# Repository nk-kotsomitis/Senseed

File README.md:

## Introduction

Senseed, a Smart Agriculture IoT System, is an end-to-end IoT solution designed to monitor and manage agricultural environments. This repository includes the **firmware**, **hardware**, **enclosures**, and **server setup** required to deploy the system.<br>
<br>
<br>
<div align="center">
  
</div>
<br>
<br>

## System Overview
This system leverages a wireless sensor network in a star topology, using **NRF24L01** modules operating at 2.4GHz for communication. The network comprises soil and environmental sensors that gather data and transmit it to a central gateway. The gateway serves as the primary hub, collecting sensor data and communicating with the controllers to make real-time adjustments. <br>
<br>
For data processing and storage, the gateway connects to an Ubuntu server over **WiFi**, using the **MQTT** protocol with **RabbitMQ** as the message broker. On the server side, **InfluxDB** is used for time-series data storage. <br>

<br>
<br>
<div align="center">
  
</div>
<br>
<br>

The gateway is powered by an **ATMEGA1284** and connects to the internet via an **ESP32** module, utilizing AT commands. The sensors and controllers in the system are based on the **ATMEGA328P** microcontroller. <br>
<br>
The environmental sensor is optimized for low-power operation, measuring temperature and humidity with a high-precision SHT40 sensor while also monitoring battery voltage to ensure reliable performance over extended periods. <br>
<br>
The soil sensor assesses soil moisture levels using a moisture probe. <br>
<br>
The controllers are designed for both low and high-power applications, managing devices through relay control. Each controller is equipped with a battery-powered real-time clock (RTC) to maintain accurate time in case of power outages. The high-power controller additionally monitors current consumption using an ACS712 sensor for enhanced energy management.

<br>
<br>

**IMPORTANT NOTE: This repository contains a proof-of-concept implementation and is intended for demonstration purposes to showcase architecture design and coding practices. Some components are intentionally missing or incomplete, so the system is not production-ready.**

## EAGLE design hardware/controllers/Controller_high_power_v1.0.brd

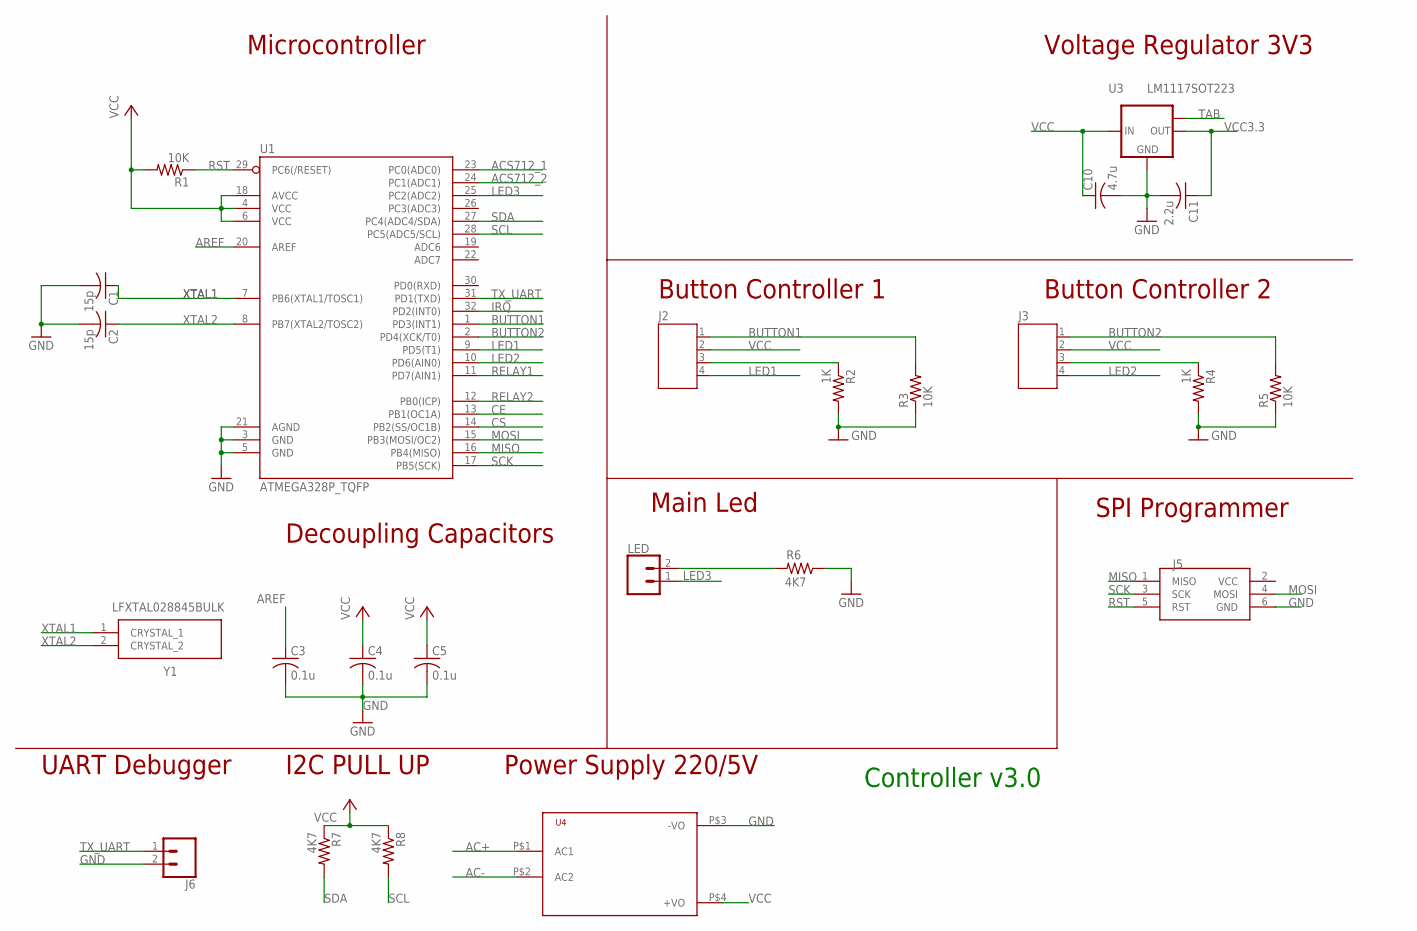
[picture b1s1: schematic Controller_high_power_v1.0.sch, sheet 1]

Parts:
C1, C2: 15p; SMD-0805
C3, C4, C5: 0.1u; SMD-0805
C10: 4.7u; SMD-0805
C11: 2.2u; SMD-0805
J2, J3: JST-PH4
J5: ISP; AVRISP
J6: CONN_02; 1X02
LED: CONN_02; 1X02
R1, R3, R5: 10K; SMD-0805
R2, R4: 1K; SMD-0805
R6, R7, R8: 4K7; SMD-0805
U1: ATMEGA328P_TQFP; TQFP32-08
U3: LM1117SOT223; SOT223
U4: HKLPM01
Y1: LFXTAL028845BULK

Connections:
AC+: U4.P$1 (AC1); also elsewhere on the board
AC-: U4.P$2 (AC2); also elsewhere on the board
ACS712_1: U1.23 (PC0(ADC0)); also elsewhere on the board
ACS712_2: U1.24 (PC1(ADC1)); also elsewhere on the board
AREF: C3.1, U1.20 (AREF)
BUTTON1: J2.1, R3.2, U1.1 (PD3(INT1))
BUTTON2: J3.1, R5.2, U1.2 (PD4(XCK/T0))
CE: U1.13 (PB1(OC1A)); also elsewhere on the board
CS: U1.14 (PB2(SS/OC1B)); also elsewhere on the board
GND: C1.2, C2.2, C3.2, C4.2, C5.2, C10.2, C11.2, J5.6 (GND), J6.2, R2.2, R3.1, R4.2, R5.1, R6.1, U1.3 (GND), U1.5 (GND), U1.21 (AGND), U3.1 (GND), U4.P$3 (-VO); also elsewhere on the board
IRQ: U1.32 (PD2(INT0)); also elsewhere on the board
LED1: J2.4, U1.9 (PD5(T1))
LED2: J3.4, U1.10 (PD6(AIN0))
LED3: LED.1, U1.25 (PC2(ADC2))
MISO: J5.1 (MISO), U1.16 (PB4(MISO)); also elsewhere on the board
MOSI: J5.4 (MOSI), U1.15 (PB3(MOSI/OC2)); also elsewhere on the board
unnamed: LED.2, R6.2
unnamed: J2.3, R2.1
unnamed: J3.3, R4.1
RELAY1: U1.11 (PD7(AIN1)); also elsewhere on the board
RELAY2: U1.12 (PB0(ICP)); also elsewhere on the board
RST: J5.5 (RST), R1.1, U1.29 (PC6(/RESET))
SCK: J5.3 (SCK), U1.17 (PB5(SCK)); also elsewhere on the board
SCL: R8.2, U1.28 (PC5(ADC5/SCL)); also elsewhere on the board
SDA: R7.2, U1.27 (PC4(ADC4/SDA)); also elsewhere on the board
TAB: U3.TAB (OUT1)
TX_UART: J6.1, U1.31 (PD1(TXD))
VCC: C4.1, C5.1, C10.1, J2.2, J3.2, J5.2 (VCC), R1.2, R7.1, R8.1, U1.4 (VCC), U1.6 (VCC), U1.18 (AVCC), U3.3 (IN), U4.P$4 (+VO); also elsewhere on the board
VCC3.3: C11.1, U3.2 (OUT); also elsewhere on the board
XTAL1: C1.1, U1.7 (PB6(XTAL1/TOSC1)), Y1.1 (CRYSTAL_1)
XTAL2: C2.1, U1.8 (PB7(XTAL2/TOSC2)), Y1.2 (CRYSTAL_2)

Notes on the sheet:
Controller v3.0
Decoupling Capacitors
Voltage Regulator 3V3
Microcontroller
UART Debugger
SPI Programmer
I2C PULL UP
Main Led
Button Controller 1
Power Supply 220/5V
Button Controller 2

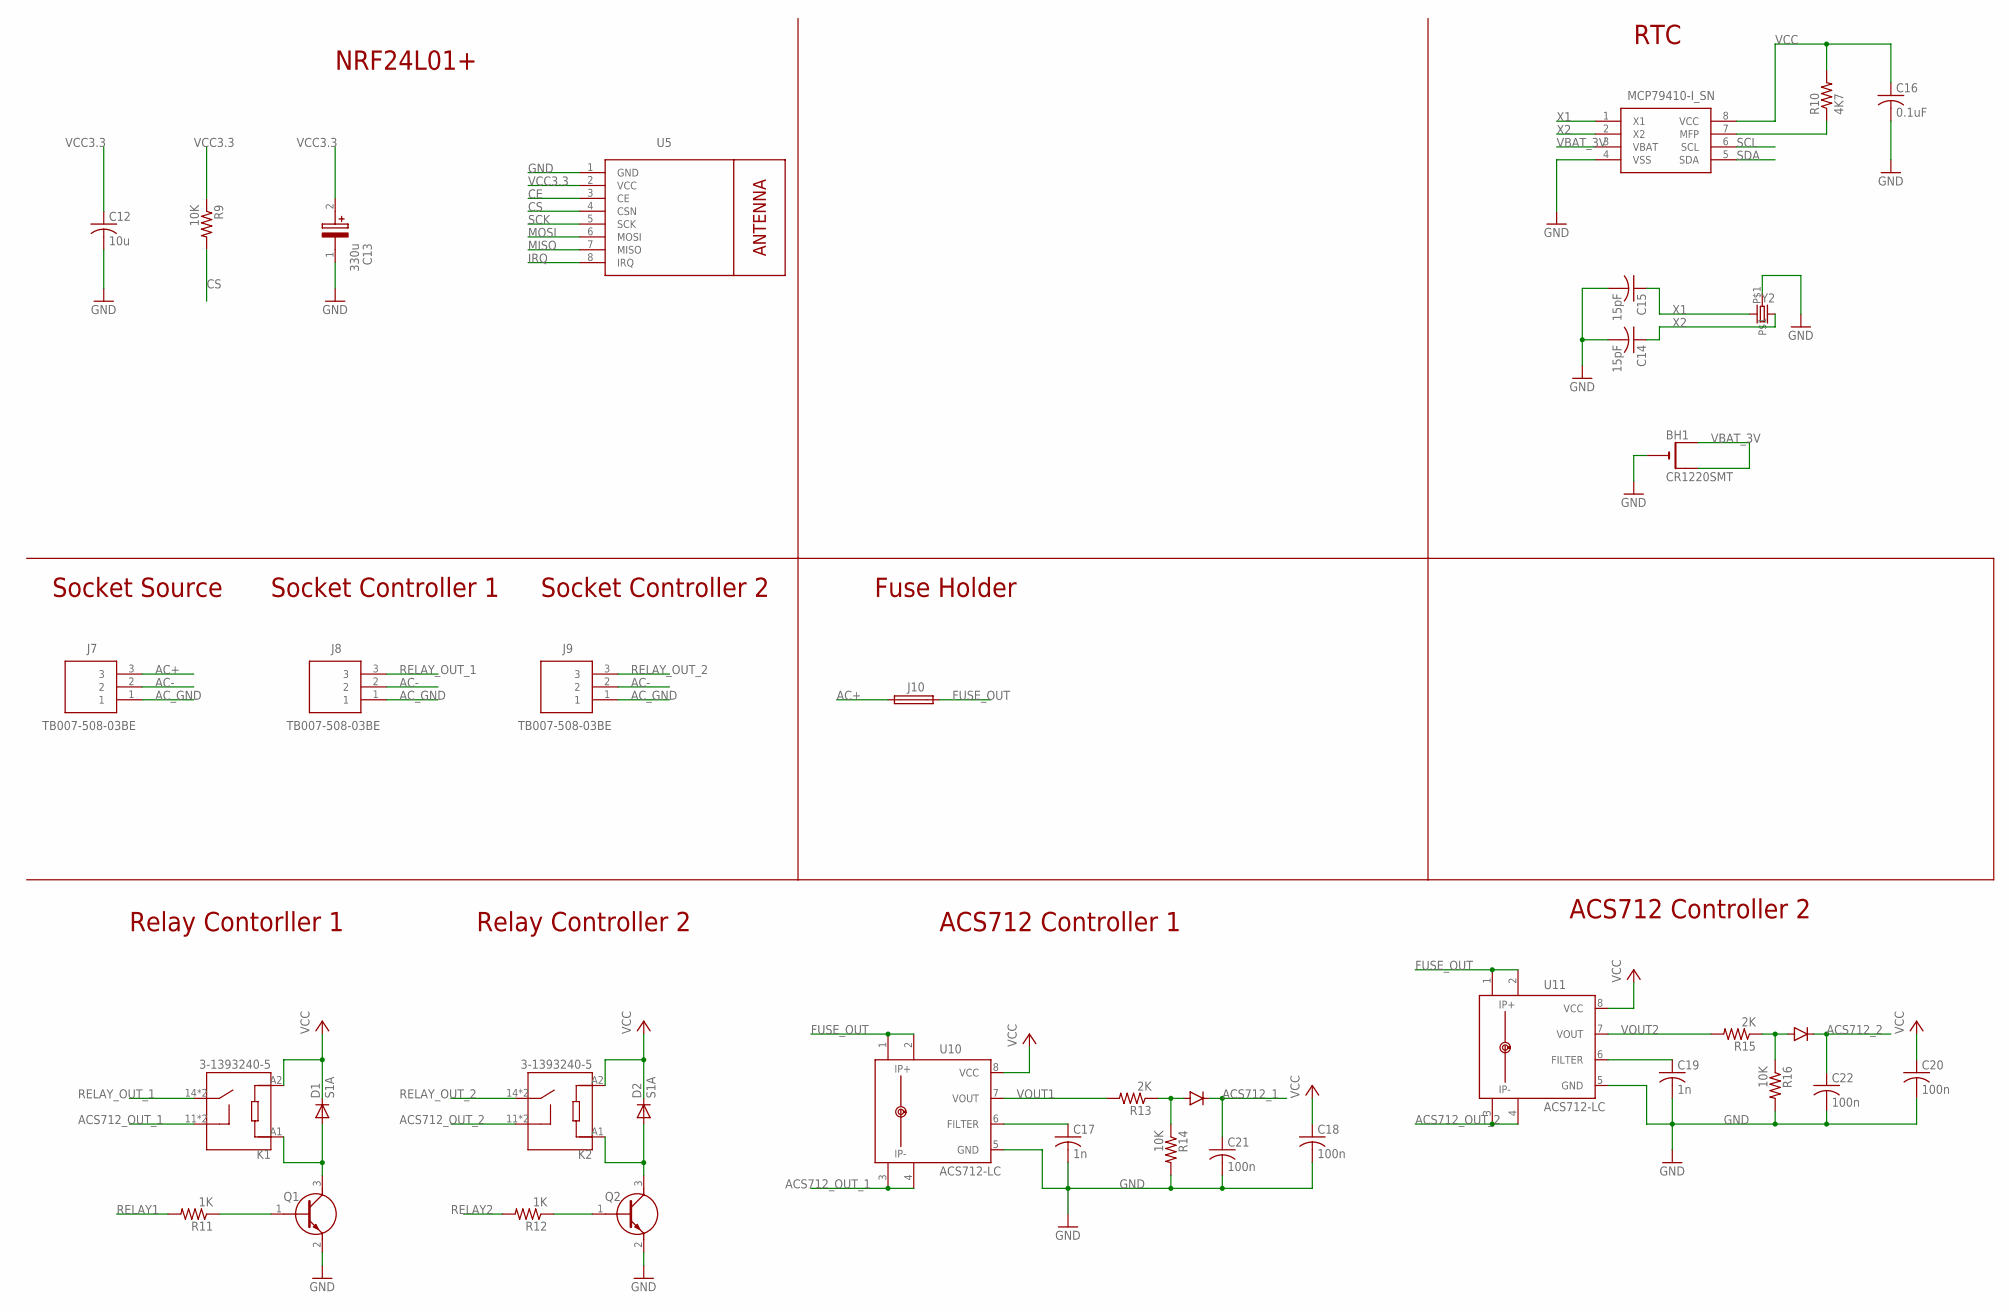
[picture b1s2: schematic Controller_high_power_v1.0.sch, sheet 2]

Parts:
BH1: CR1220SMT; CR1220-SMD
C12: 10u; SMD-0805
C13: 330u; SMD_LYTIC_D8
C14, C15: 15pF; SMD-0805
C16: 0.1uF; SMD-0805
C17, C19: 1n; SMD-0805
C18, C20, C21, C22: 100n; SMD-0805
D1, D2: S1A; DO214AC
D3, D4: DIODE; SOD-323
J7, J8, J9: TB007-508-03BE; TB00750803BE
J10: SH22,5A
K1, K2: 3-1393240-5; TE_3-1393240-5
Q1, Q2: MMBT2222A-TP; SI2305TP
R9, R14, R16: 10K; SMD-0805
R10: 4K7; SMD-0805
R11, R12: 1K; SMD-0805
R13, R15: 2K; SMD-0805
U5: WIRELESS-NRF24L01
U6: MCP79410-I_SN; SOIC127P600X175-8N
U10, U11: ACS712-LC; SOIC8
Y2: CRYSTALTC26H; TC26H

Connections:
AC+: J7.3, J10.1; also elsewhere on the board
AC-: J7.2, J8.2, J9.2; also elsewhere on the board
ACS712_1: C21.1, D3.C; also elsewhere on the board
ACS712_2: C22.1, D4.C; also elsewhere on the board
ACS712_OUT_1: K1.11, K1.11-1 (11), U10.3 (IP-), U10.4 (IP-1)
ACS712_OUT_2: K2.11, K2.11-1 (11), U11.3 (IP-), U11.4 (IP-1)
AC_GND: J7.1, J8.1, J9.1
CE: U5.3 (CE); also elsewhere on the board
CS: R9.2, U5.4 (CSN); also elsewhere on the board
FUSE_OUT: J10.2, U10.1 (IP+), U10.2 (IP+1), U11.1 (IP+), U11.2 (IP+1)
GND: BH1.-, C12.2, C13.1, C14.2, C15.2, C16.2, C17.2, C18.2, C19.2, C20.2, C21.2, C22.2, Q1.2 (E), Q2.2 (E), R14.2, R16.2, U5.1 (GND), U6.4 (VSS), U10.5 (GND), U11.5 (GND), Y2.P$1; also elsewhere on the board
IRQ: U5.8 (IRQ); also elsewhere on the board
MISO: U5.7 (MISO); also elsewhere on the board
MOSI: U5.6 (MOSI); also elsewhere on the board
unnamed: Q2.1 (B), R12.1
unnamed: D2.A, K2.A1, Q2.3 (C)
unnamed: D1.A, K1.A1, Q1.3 (C)
unnamed: C19.1, U11.6 (FILTER)
unnamed: C17.1, U10.6 (FILTER)
unnamed: Q1.1 (B), R11.1
unnamed: D4.A, R15.1, R16.1
unnamed: D3.A, R13.1, R14.1
unnamed: R10.1, U6.7 (MFP)
RELAY1: R11.2; also elsewhere on the board
RELAY2: R12.2; also elsewhere on the board
RELAY_OUT_1: J8.3, K1.14, K1.14-1 (14)
RELAY_OUT_2: J9.3, K2.14, K2.14-1 (14)
SCK: U5.5 (SCK); also elsewhere on the board
SCL: U6.6 (SCL); also elsewhere on the board
SDA: U6.5 (SDA); also elsewhere on the board
VBAT_3V: BH1.+$1 (+), BH1.+$2 (+1), U6.3 (VBAT)
VCC: C16.1, C18.1, C20.1, D1.C, D2.C, K1.A2, K2.A2, R10.2, U6.8 (VCC), U10.8 (VCC), U11.8 (VCC); also elsewhere on the board
VCC3.3: C12.1, C13.2, R9.1, U5.2 (VCC); also elsewhere on the board
VOUT1: R13.2, U10.7 (VOUT)
VOUT2: R15.2, U11.7 (VOUT)
X1: C15.1, U6.1 (X1), Y2.2
X2: C14.1, U6.2 (X2), Y2.1

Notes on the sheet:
NRF24L01+
Relay Contorller 1
ACS712 Controller 1
Socket Source
Fuse Holder
RTC
Relay Controller 2
Socket Controller 1
Socket Controller 2
ACS712 Controller 2

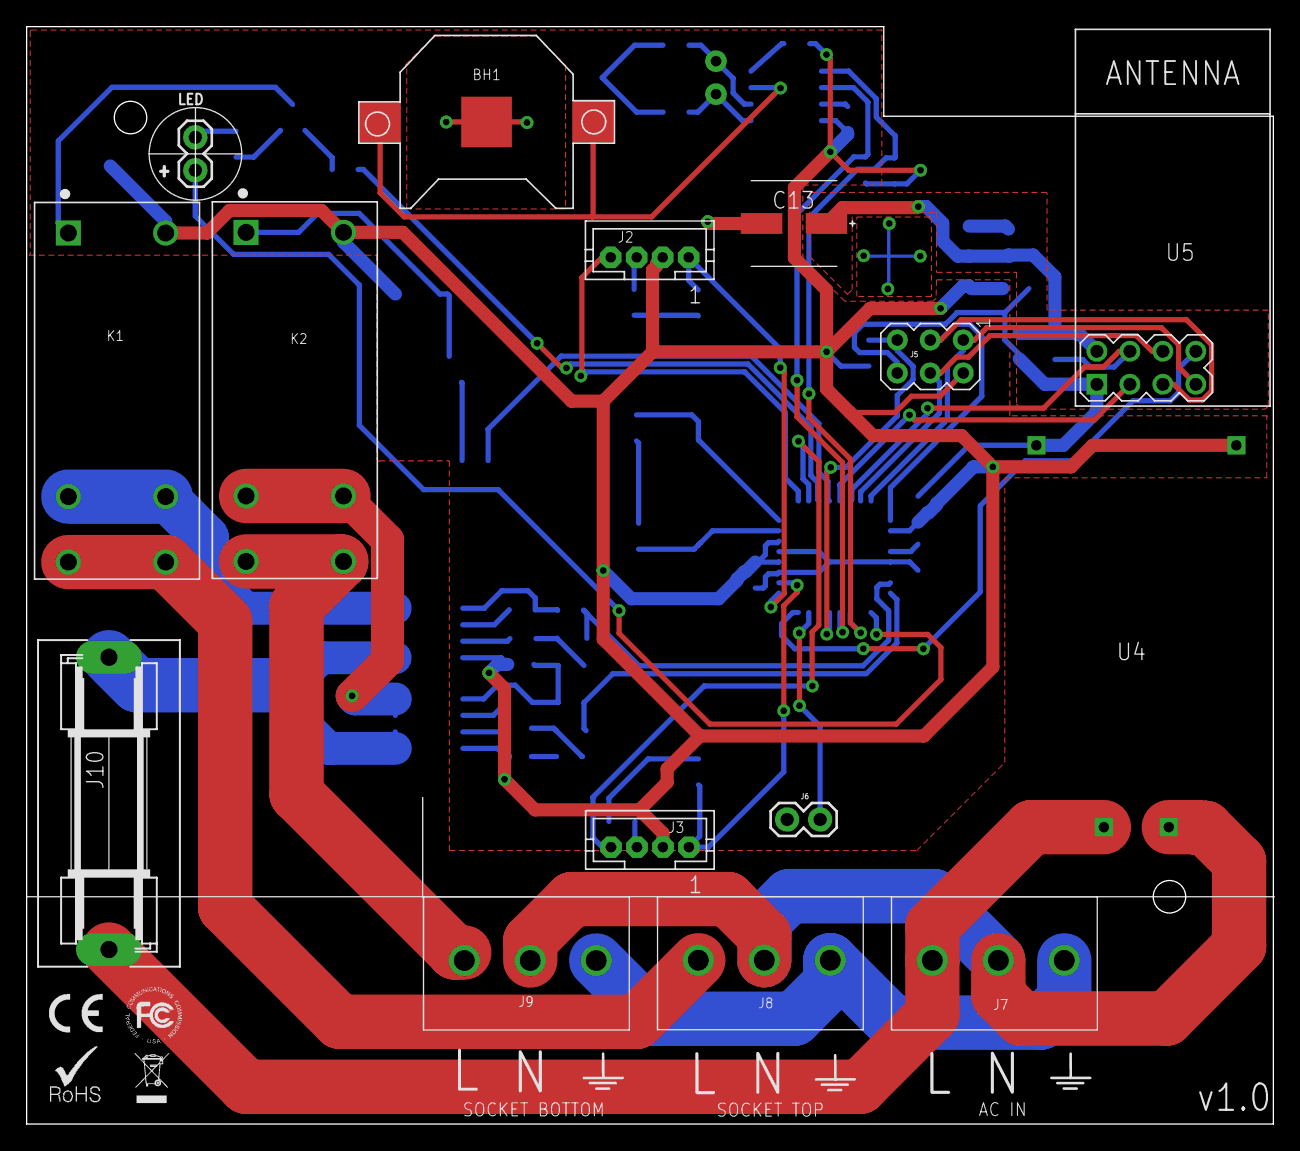
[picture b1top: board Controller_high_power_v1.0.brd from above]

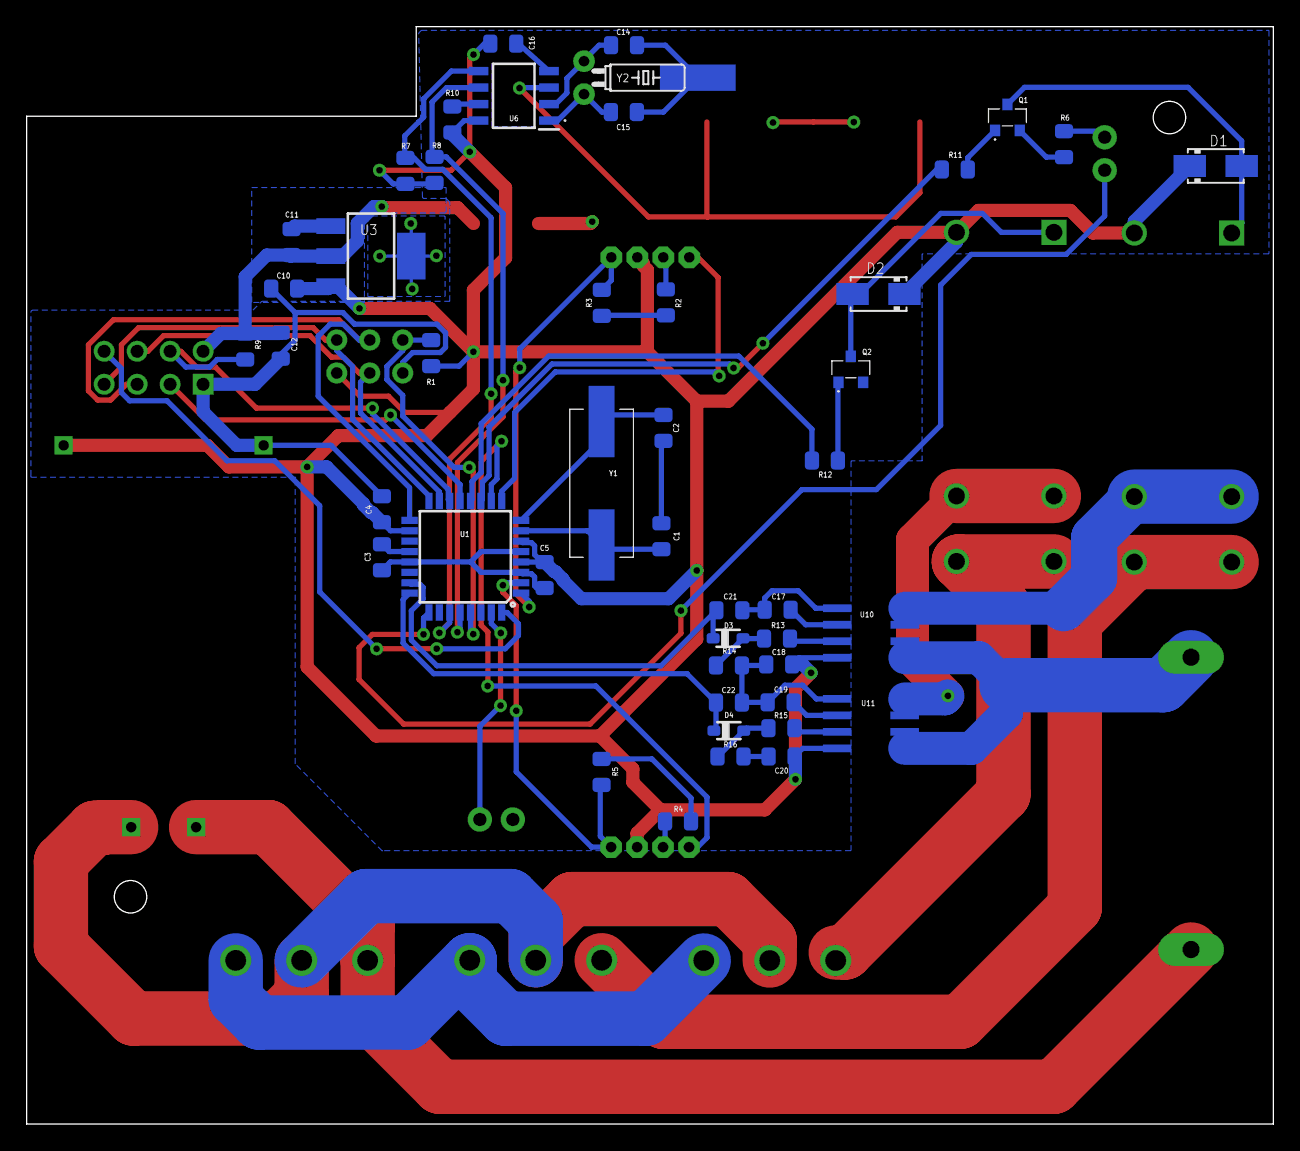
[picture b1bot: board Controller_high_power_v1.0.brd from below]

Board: 2 copper layers, 96.0 x 84.5 mm, 61 parts (46 on the bottom side), 50 nets.

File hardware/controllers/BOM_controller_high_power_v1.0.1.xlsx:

# | Reference Designators | Quantity | MPN | Manufacturer | Part Description | Value | Package | Remark or Link
1 | U1 | 1 | ATMEGA328P-AU | Microchip Technology / Atmel | 8-bit Microcontrollers - MCU 32KB In-system Flash 20MHz 1.8V-5.5V | ATMEGA328P_TQFP | TQFP-32
2 | U3 | 1 | SPX1117M3-L-3-3/TR | Maxlinear | LDO Voltage Regulators 3.3V 0.8A Positive | 3.3V 0.8A | SOT-223-3+A4:H4
3 | U4 | 1 | HLK-PM01 | Hi-Link | AC-DC 220V to 5V 3W Step-Down Power Supply Module | 220V to 5V | Through Hole
4 | U5 | 1 | - | - | NRF24L01+ 2.4GHz Wireless RF Transceiver Module | - | Plug In Module - 2x4 2.54mm header | Customer Provided
5 | U6 | 1 | MCP79410T-I/SN | Microchip Technology | Real Time Clock I2C GP RTCC 1Kb EE 64B SRAM ID | - | SOIC-8
6 | BH1 | 1 | MY-1220-03 | MYOUNG | Coin Cell Battery Holder CR1220 SMT | - | SMD
7 | K1, K2 | 2 | G2RL-1A-E-ASI DC5 | Omron Electronics | General Purpose Relays 1 form A w/ TV3 5VDC Coil, 16A | Power Relays | Through Hole
8 | U10, U11 | 2 | ACS712ELCTR-20A-T | ALLEGRO MICROSYSTEMS | Linear Current Sensor, Hall Effect, 20A Sensing Current, SOIC-8 | 100mV/A output | SOIC-8
9 | Y1 | 1 | TAXM4M2ILFBET2T | TAE(Zhejiang Abel Elec) | ±30ppm -20℃~70℃ 49SMD 20pF 80Ω 4000000Hz HC-49S/SMD Crystals | 4 MHz | HC-49/S
10 | Y2 | 1 | JFWSH32K25A104C | SHENZHEN JINGFA ELECTRONICS | Radial Cylinder Crystal 32.768KHz ±20ppm 12.5pF 30 KOhm(Max) Radial,3x8mm | 32.768 kHz | OSC-TH Radial 3x8mm
11 | J2, J3 | 2 | PH2.0-4P | CAX | 4-Pin Low-profile PH2.0 Housing Connector | 4 Position | Through Hole
12 | LED | 1 | 204-10SUGC/S400-A5-L | Everlight Elec | Green 525nm Through Hole 3mm Light Emitting Diodes (LED) - Water Clear | 3mm Green - Clear | Through Hole
13 | LED | 1 | ERM 1-1.140 | Bivar | LED Mounting Hardware LED Mount Self Ret Universal LED Black | T-1 3/4 (5mm) | LED Mounts
14 | J5 | 1 | C65114 | BOOMELE(Boom Precision Elec) | 2 2.54mm 6 Straight Header，Breakaway P=2.54mm Pin Headers | 6 Position | Through Hole
15 | J6 | 1 | PZ254V-11-02P | XFCN | 2.54mm Straight 2 1 Header，Breakaway Through Hole,P=2.54mm Pin Headers | 2 Position | Through Hole
16 | J7, J8, J9 | 3 | WJ500V-5.08-3P | Ningbo Kangnex Elec | PCB Screw Terminal Block Connector 5.08mm Pitch 3 Poles Vertical | 3 Position | Through Hole
17 | J10 | 1 | PTF-77 | XFCN | Fuse Holder 5x20 | - | SH22,5A
18 | Q1, Q2 | 2 | MMBT2222A |  | (BJT) NPN 600mA 40V SURFACE MOUNT TRANSISTOR | NPN | SOT23-3
19 | D1, D2 | 2 | 1N4007F (M7) |  | Silicon Rectifier Diode 1A 1000V SMA | 1A 1000V | SMA / DO-214AC
20 | D3, D4 | 2 | 1N4448WS-7-F | Diodes Incorporated | Diodes - General Purpose, Power, Switching Vr/75V Io/250mA T/R | 75 V | SOD-323
21 | C1, C2, C14, C15 | 4 | 0805CG150J500NT |  | Multilayer Ceramic Capacitor MLCC 15pF ±5% 0805 SMD | 15pF | 0805
22 | C3, C4, C5, C16, C18, C20, C21, C22 | 8 | 0805B104M500NT |  | Multilayer Ceramic Capacitor MLCC 100nF ±5% 0805 SMD | 100nF | 0805
23 | C11 | 1 | CL21B225KOFNNNE |  | Multilayer Ceramic Capacitor MLCC 2.2uF X7R ±10% 16V 0805 SMD | 2.2uF | 0805
24 | C10 | 1 | CL21A475KAQNNNE |  | Multilayer Ceramic Capacitor MLCC 4.7uF X5R ±10% 25V 0805 SMD | 4.7uF | 0805
25 | C12 | 1 | GRM21BR61C106KE15L |  | X5R ±10% 16V 10uF 0805 Multilayer Ceramic Capacitors MLCC - SMD/SMT | 10uF | 0805
26 | C13 | 1 | VD1A331ME077000CE0 | Changzhou Huawei Electronics | 6.3mm 330uF 7.7mm 10V 2000hrs 105℃ ±20% -45℃~+105℃ SMD,6.3x7.7mm Aluminum Elect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 | 330uF | 6.3x7.7 SMD
27 | C17, C19 | 2 | CC0805KRX7R9BB102 |  | 50V 1nF X7R ±10% 0805 Multilayer Ceramic Capacitors MLCC - SMD/SMT | 1nF | 0805
28 | R1, R3, R5, R9, R14, R16 | 6 | RC0805FR-7W10KL |  | Chip Resistor - Surface Mount 10K ±1% 1/4W 0805 | 10K 1/4W | 0805
29 | R2, R4, R11, R12 | 4 | 0805W8J1001T5E |  | Chip Resistor - Surface Mount 1K ±5% 1/8W 0805 | 1K | 0805
30 | R13, R15 | 2 | 0805W8J2001T5E |  | Chip Resistor - Surface Mount 2K ±5% 1/8W 0805 | 2K | 0805
31 | R6, R7, R8, R10 | 4 | 0805W8J0472T5E |  | Chip Resistor - Surface Mount 4.7K ±5% 1/8W 0805 | 4K7 | 0805
 | Off-board components
32 | - | 1 | CMC_313_GTP | Visual Communications Company (VCC) | LED Lenses Green Diffused 5mm CMC313GTP | Green | -
33 | - | 2 | TC013-N11ASKKUGXX | Well Buying | Tactile Switches TACTILE/JOG SWITCH SPST50mA 12VDC180gf | Illuminated | -
34 | - | 2 | - |  | PH2.0 PH 2.0 4pin PH-4p connector with cable 100mm wire 24AWG | PH-4p 100mm 24AWG | -
35 | - | 1 | 0218015.MXP |  | 250V 15A Glass Tube Fuse Slow Blow,5x20mm Fuses | 15 A | -

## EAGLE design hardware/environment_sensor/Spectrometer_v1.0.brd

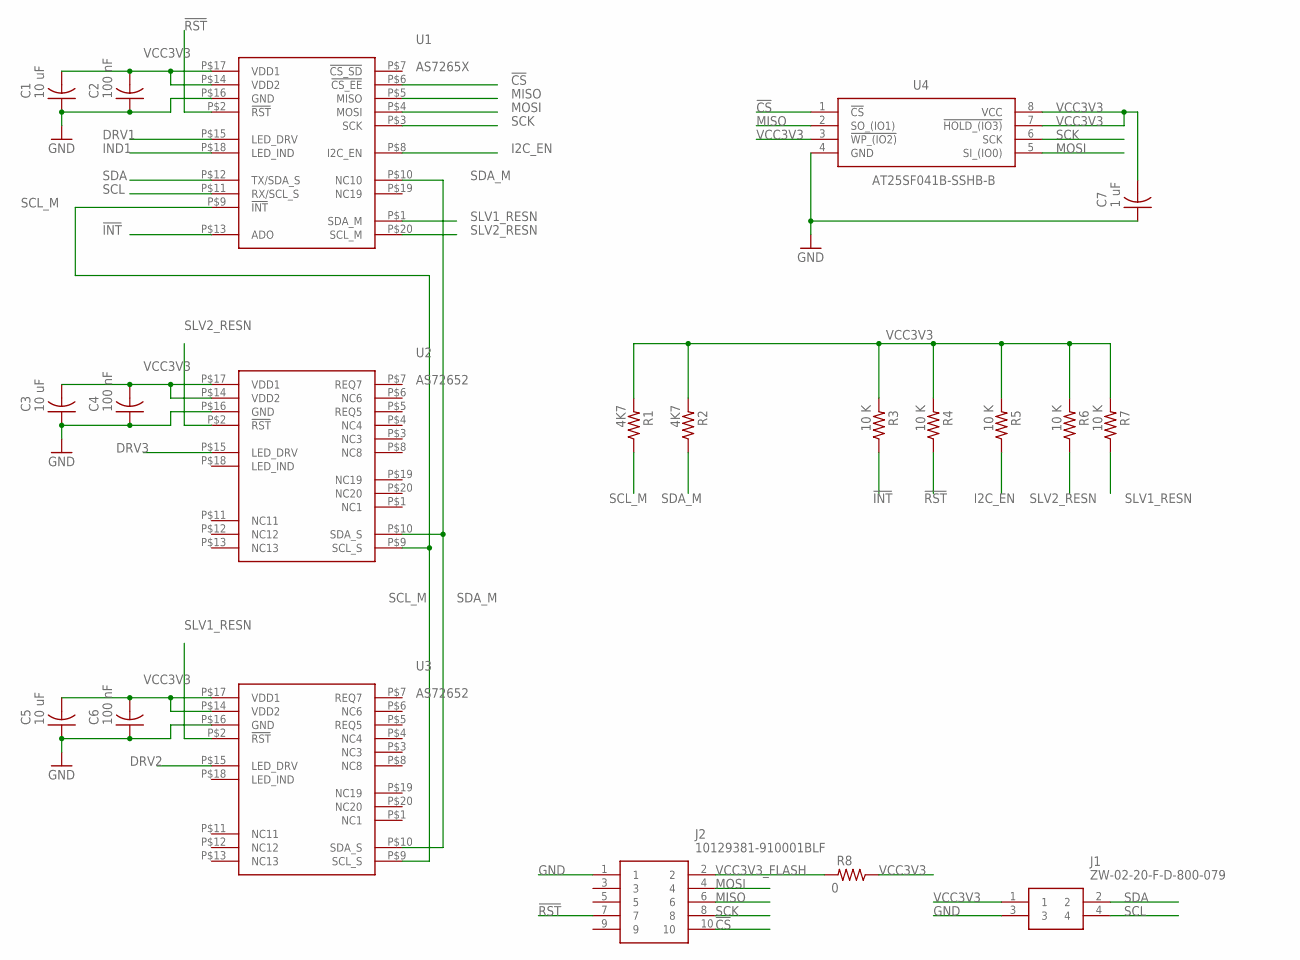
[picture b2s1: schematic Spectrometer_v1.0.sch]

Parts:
C1, C3, C5: 10 uF; SMD-0805
C2, C4, C6: 100 nF; SMD-0805
C7: 1 uF; SMD-0805
J1: ZW-02-20-F-D-800-079; HDRV4W64P254_2X2_508X508X2669P
J2: 10129381-910001BLF; HDRV10W67P254_2X5_1270X483X858
R1, R2: 4K7; SMD-0805
R3, R4, R5, R6, R7: 10 K; SMD-0805
R8: 0; SMD-0805
U1: AS7265X
U2, U3: AS72652; AS7265X
U4: AT25SF041B-SSHB-B; SOIC127P600X175-8N

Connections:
!CS: J2.10, U1.P$6 (!CS_EE), U4.1 (!CS)
!INT: R3.1, U1.P$13 (ADO)
!RST: J2.7, R4.1, U1.P$2 (!RST)
DRV1: U1.P$15 (LED_DRV)
DRV2: U3.P$15 (LED_DRV)
DRV3: U2.P$15 (LED_DRV)
GND: C1.1, C2.1, C3.1, C4.1, C5.1, C6.1, C7.1, J1.3, J2.1, U1.P$16 (GND), U2.P$16 (GND), U3.P$16 (GND), U4.4 (GND)
I2C_EN: R5.1, U1.P$8 (I2C_EN)
IND1: U1.P$18 (LED_IND)
MISO: J2.6, U1.P$5 (MISO), U4.2 (SO_(IO1))
MOSI: J2.4, U1.P$4 (MOSI), U4.5 (SI_(IO0))
SCK: J2.8, U1.P$3 (SCK), U4.6 (SCK)
SCL: J1.4, U1.P$11 (RX/SCL_S)
SCL_M: R1.1, U1.P$9 (!INT), U2.P$9 (SCL_S), U3.P$9 (SCL_S)
SDA: J1.2, U1.P$12 (TX/SDA_S)
SDA_M: R2.1, U1.P$10 (NC10), U2.P$10 (SDA_S), U3.P$10 (SDA_S)
SLV1_RESN: R7.1, U1.P$1 (SDA_M), U3.P$2 (!RST)
SLV2_RESN: R6.1, U1.P$20 (SCL_M), U2.P$2 (!RST)
VCC3V3: C1.2, C2.2, C3.2, C4.2, C5.2, C6.2, C7.2, J1.1, R1.2, R2.2, R3.2, R4.2, R5.2, R6.2, R7.2, R8.1, U1.P$14 (VDD2), U1.P$17 (VDD1), U2.P$14 (VDD2), U2.P$17 (VDD1), U3.P$14 (VDD2), U3.P$17 (VDD1), U4.3 (!WP_(IO2)), U4.7 (!HOLD_(IO3)), U4.8 (VCC)
VCC3V3_FLASH: J2.2, R8.2

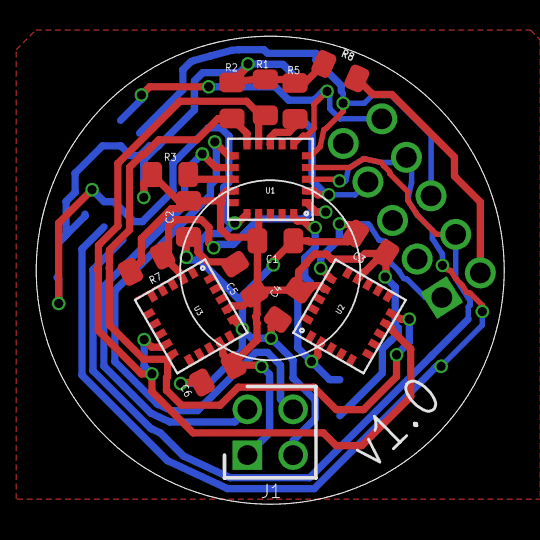
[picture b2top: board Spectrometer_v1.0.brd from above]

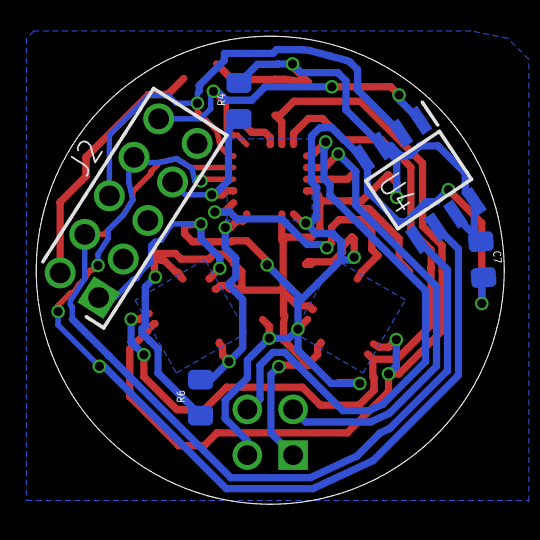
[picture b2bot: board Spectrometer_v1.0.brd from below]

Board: 2 copper layers, 26.0 x 26.0 mm, 21 parts (5 on the bottom side), 16 nets.

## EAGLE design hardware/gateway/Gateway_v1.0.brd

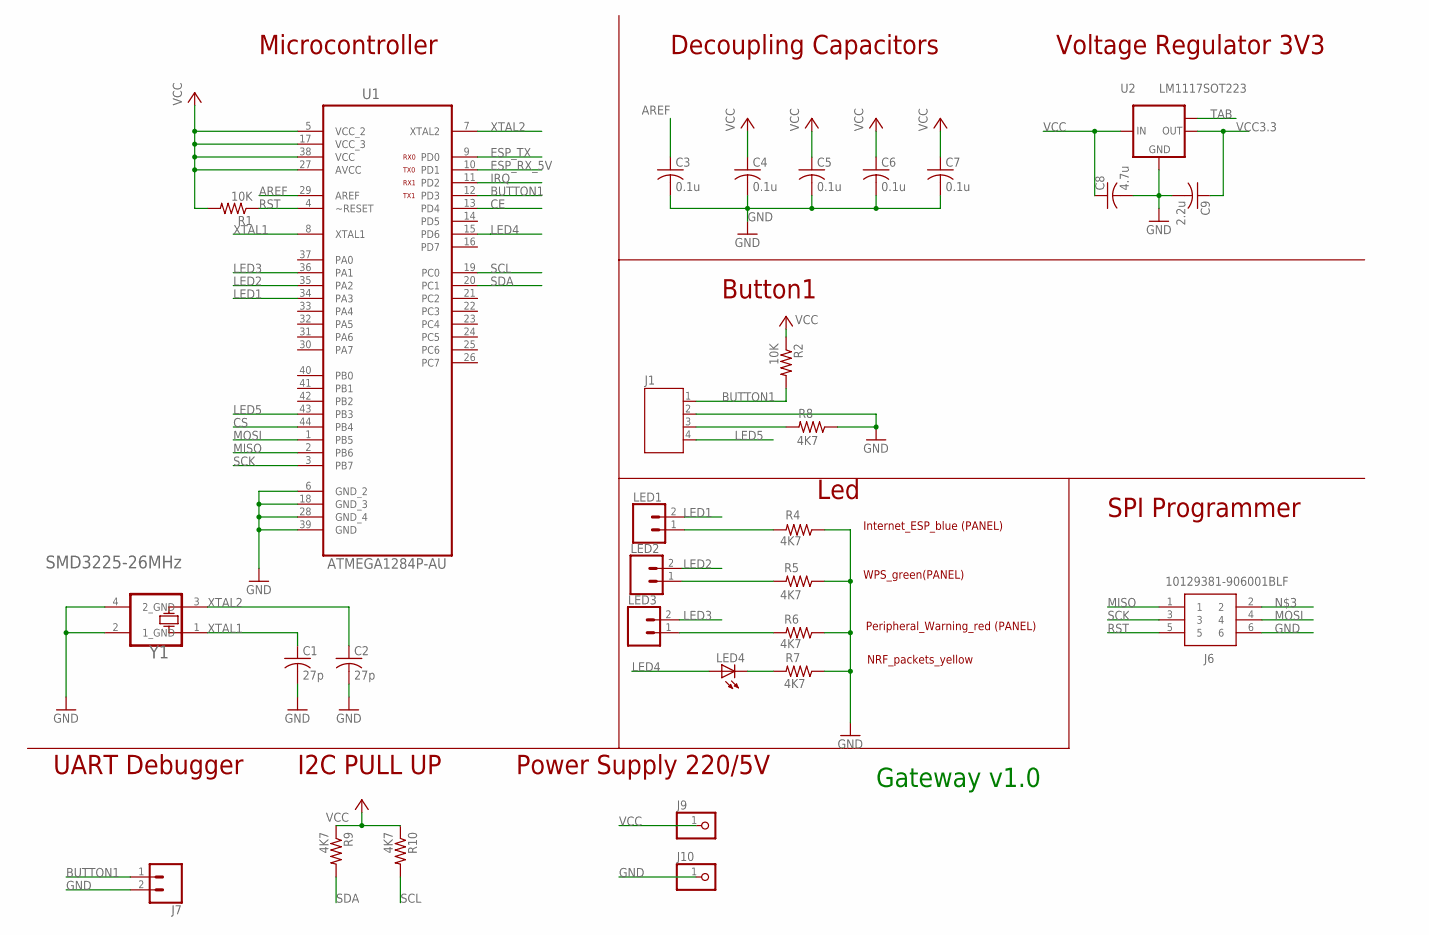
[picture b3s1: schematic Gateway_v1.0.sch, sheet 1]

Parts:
C1, C2: 27p; SMD-0805
C3, C4, C5, C6, C7: 0.1u; SMD-0805
C8: 4.7u; SMD-0805
C9: 2.2u; SMD-0805
J1: JST-PH4
J6: 10129381-906001BLF; HDRV6W67P254_2X3_762X483X858P
J7: CONN_02; 1X02
J9, J10: PINHD-1X1CB; 1X01-CLEANBIG
LED1, LED2, LED3: CONN_02; 1X02
LED4: LED4; SMD-0805-LED
R1, R2: 10K; SMD-0805
R4, R5, R6, R7, R8, R9, R10: 4K7; SMD-0805
U1: ATMEGA1284P-AU; QFP80P1200X1200X120-44N
U2: LM1117SOT223; SOT223
Y1: TND_ELECTRONIC_SMD3225-26MHZTND_ELECTRONIC_SMD322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; TND_ELECTRONIC_SMD3225-26MHZ_0

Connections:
AREF: C3.1, U1.29 (AREF)
BUTTON1: J1.1, J7.1, R2.2, U1.12 (PD3)
CE: U1.13 (PD4); also elsewhere on the board
CS: U1.44 (PB4); also elsewhere on the board
ESP_RX_5V: U1.10 (PD1); also elsewhere on the board
ESP_TX: U1.9 (PD0); also elsewhere on the board
GND: C1.2, C2.2, C3.2, C4.2, C5.2, C6.2, C7.2, C8.2, C9.2, J1.2, J6.6, J7.2, J10.1, R4.1, R5.1, R6.1, R7.1, R8.1, U1.6 (GND_2), U1.18 (GND_3), U1.28 (GND_4), U1.39 (GND), U2.1 (GND), Y1.2 (1_GND), Y1.4 (2_GND); also elsewhere on the board
IRQ: U1.11 (PD2); also elsewhere on the board
LED1: LED1.2, U1.34 (PA3)
LED2: LED2.2, U1.35 (PA2)
LED3: LED3.2, U1.36 (PA1)
LED4: LED4.1 (A), U1.15 (PD6)
LED5: J1.4, U1.43 (PB3)
MISO: J6.1, U1.2 (PB6); also elsewhere on the board
MOSI: J6.4, U1.1 (PB5); also elsewhere on the board
unnamed: LED2.1, R5.2
unnamed: LED3.1, R6.2
unnamed: LED1.1, R4.2
unnamed: J1.3, R8.2
unnamed: LED4.2 (C), R7.2
RST: J6.5, R1.1, U1.4 (~RESET)
SCK: J6.3, U1.3 (PB7); also elsewhere on the board
SCL: R10.2, U1.19 (PC0); also elsewhere on the board
SDA: R9.2, U1.20 (PC1); also elsewhere on the board
VCC: C4.1, C5.1, C6.1, C7.1, C8.1, J9.1, R1.2, R2.1, R9.1, R10.1, U1.5 (VCC_2), U1.17 (VCC_3), U1.27 (AVCC), U1.38 (VCC), U2.3 (IN); also elsewhere on the board
VCC3.3: C9.1, U2.2 (OUT); also elsewhere on the board
XTAL1: C1.1, U1.8 (XTAL1), Y1.1 (X1)
XTAL2: C2.1, U1.7 (XTAL2), Y1.3 (X2)
ΤΑΒ: U2.TAB (OUT1)

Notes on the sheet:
Gateway v1.0
Decoupling Capacitors
Voltage Regulator 3V3
Microcontroller
UART Debugger
SPI Programmer
I2C PULL UP
Led
Button1
TX1
RX1
Power Supply 220/5V
Internet_ESP_blue (PANEL)
NRF_packets_yellow
Peripheral_Warning_red (PANEL)
WPS_green(PANEL)
TX0
RX0

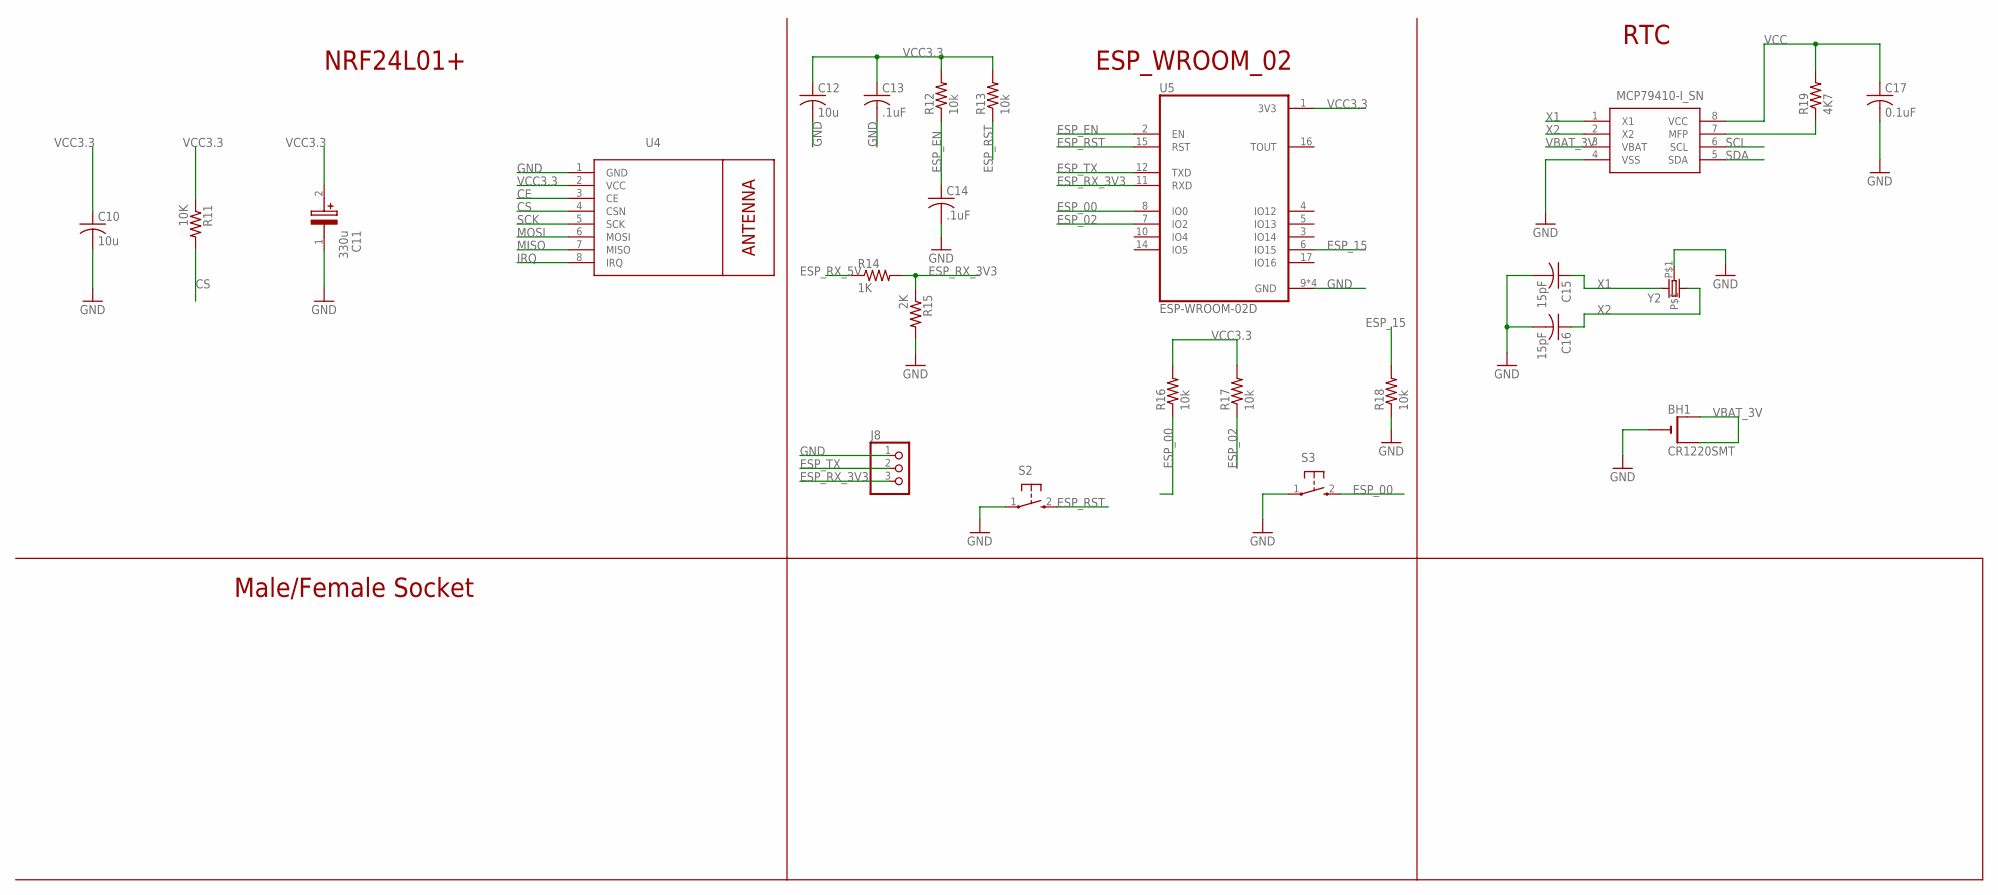
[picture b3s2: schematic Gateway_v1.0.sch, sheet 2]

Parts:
BH1: CR1220SMT; CR1220-SMD
C10, C12: 10u; SMD-0805
C11: 330u; SMD_LYTIC_D8
C13, C14: .1uF; SMD-0805
C15, C16: 15pF; SMD-0805
C17: 0.1uF; SMD-0805
J8: PINHD-1X3; 1X03
R11: 10K; SMD-0805
R12, R13, R16, R17, R18: 10k; SMD-0805
R14: 1K; SMD-0805
R15: 2K; SMD-0805
R19: 4K7; SMD-0805
S2, S3: SPST_TACT-KMR2; KMR2
U4: WIRELESS-NRF24L01
U5: ESP-WROOM-02D; MODULE_ESP-WROOM-02D
U6: MCP79410-I_SN; SOIC127P600X175-8N
Y2: CRYSTALTC26H; TC26H

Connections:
CE: U4.3 (CE); also elsewhere on the board
CS: R11.2, U4.4 (CSN); also elsewhere on the board
ESP_00: R16.1, S3.2 (S), U5.8 (IO0)
ESP_02: R17.1, U5.7 (IO2)
ESP_15: R18.2, U5.6 (IO15)
ESP_EN: C14.1, R12.1, U5.2 (EN)
ESP_RST: R13.1, S2.2 (S), U5.15 (RST)
ESP_RX_3V3: J8.3, R14.2, R15.1, U5.11 (RXD)
ESP_RX_5V: R14.1; also elsewhere on the board
ESP_TX: J8.2, U5.12 (TXD); also elsewhere on the board
GND: BH1.-, C10.2, C11.1, C12.2, C13.2, C14.2, C15.2, C16.2, C17.2, J8.1, R15.2, R18.1, S2.1, S3.1, U4.1 (GND), U5.9 (GND), U5.13 (GND), U5.18 (GND), U5.19 (GND), U6.4 (VSS), Y2.P$1; also elsewhere on the board
IRQ: U4.8 (IRQ); also elsewhere on the board
MISO: U4.7 (MISO); also elsewhere on the board
MOSI: U4.6 (MOSI); also elsewhere on the board
unnamed: R19.1, U6.7 (MFP)
SCK: U4.5 (SCK); also elsewhere on the board
SCL: U6.6 (SCL); also elsewhere on the board
SDA: U6.5 (SDA); also elsewhere on the board
VBAT_3V: BH1.+$1 (+), BH1.+$2 (+1), U6.3 (VBAT)
VCC: C17.1, R19.2, U6.8 (VCC); also elsewhere on the board
VCC3.3: C10.1, C11.2, C12.1, C13.1, R11.1, R12.2, R13.2, R16.2, R17.2, U4.2 (VCC), U5.1 (3V3); also elsewhere on the board
X1: C15.1, U6.1 (X1), Y2.2
X2: C16.1, U6.2 (X2), Y2.1

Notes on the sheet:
NRF24L01+
ESP_WROOM_02
Male/Female Socket
RTC

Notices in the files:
parts and their libraries:
diy-modules: Released under the Creative Commons Attribution 4.0 International License: http://creativecommons.org/licenses/by/4.0
SparkFun-Connectors: Licensing: Creative Commons ShareAlike 4.0 International - https://creativecommons.org/licenses/by-sa/4.0
